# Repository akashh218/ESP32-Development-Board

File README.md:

# ESP32-WROOM Development Board

## Overview

This project is a custom ESP32-WROOM development board designed for embedded systems, IoT applications, robotics, and rapid prototyping. The board integrates essential support circuitry required for programming, debugging, power management, and peripheral interfacing, providing a reliable platform for ESP32-based development.

## Features

* ESP32-WROOM module
* USB Type-C interface for power and programming
* USB-to-UART converter for firmware upload and serial debugging
* 3.3V regulated power supply
* Reset and Boot buttons
* GPIO breakout headers
* I²C expansion support
* UART communication interface
* Motor driver connectivity
* Status and power indicator LEDs
* Compact and PCB-friendly design

## Hardware Specifications

| Parameter             | Value                                      |
| --------------------- | ------------------------------------------ |
| Microcontroller       | ESP32-WROOM                                |
| Operating Voltage     | 3.3V                                       |
| Input Power           | 5V USB Type-C                              |
| Wireless Connectivity | Wi-Fi 802.11 b/g/n, Bluetooth Classic, BLE |
| Programming Interface | USB-to-UART                                |
| GPIO Access           | Available through expansion headers        |

## Applications

* Home Automation
* IoT Devices
* Robotics
* Sensor Networks
* Industrial Monitoring
* Wireless Data Acquisition
* Smart Control Systems
* Embedded Learning and Prototyping

## PCB Design

The PCB was designed to provide:

* Stable power delivery
* Reliable ESP32 operation
* Easy firmware flashing
* Expansion for future peripherals
* Compact layout suitable for custom projects

## Repository Contents

* Schematics
* PCB Layout Files
* Gerber Files
* Bill of Materials (BOM)
* Assembly Documentation
* Hardware Images

## Getting Started

1. Connect the board using a USB Type-C cable.
2. Install ESP32 drivers if required.
3. Open Arduino IDE, PlatformIO, or ESP-IDF.
4. Select the appropriate ESP32 board configuration.
5. Upload your firmware.
6. Monitor serial output for debugging.

## Author

Designed and developed by Akash.

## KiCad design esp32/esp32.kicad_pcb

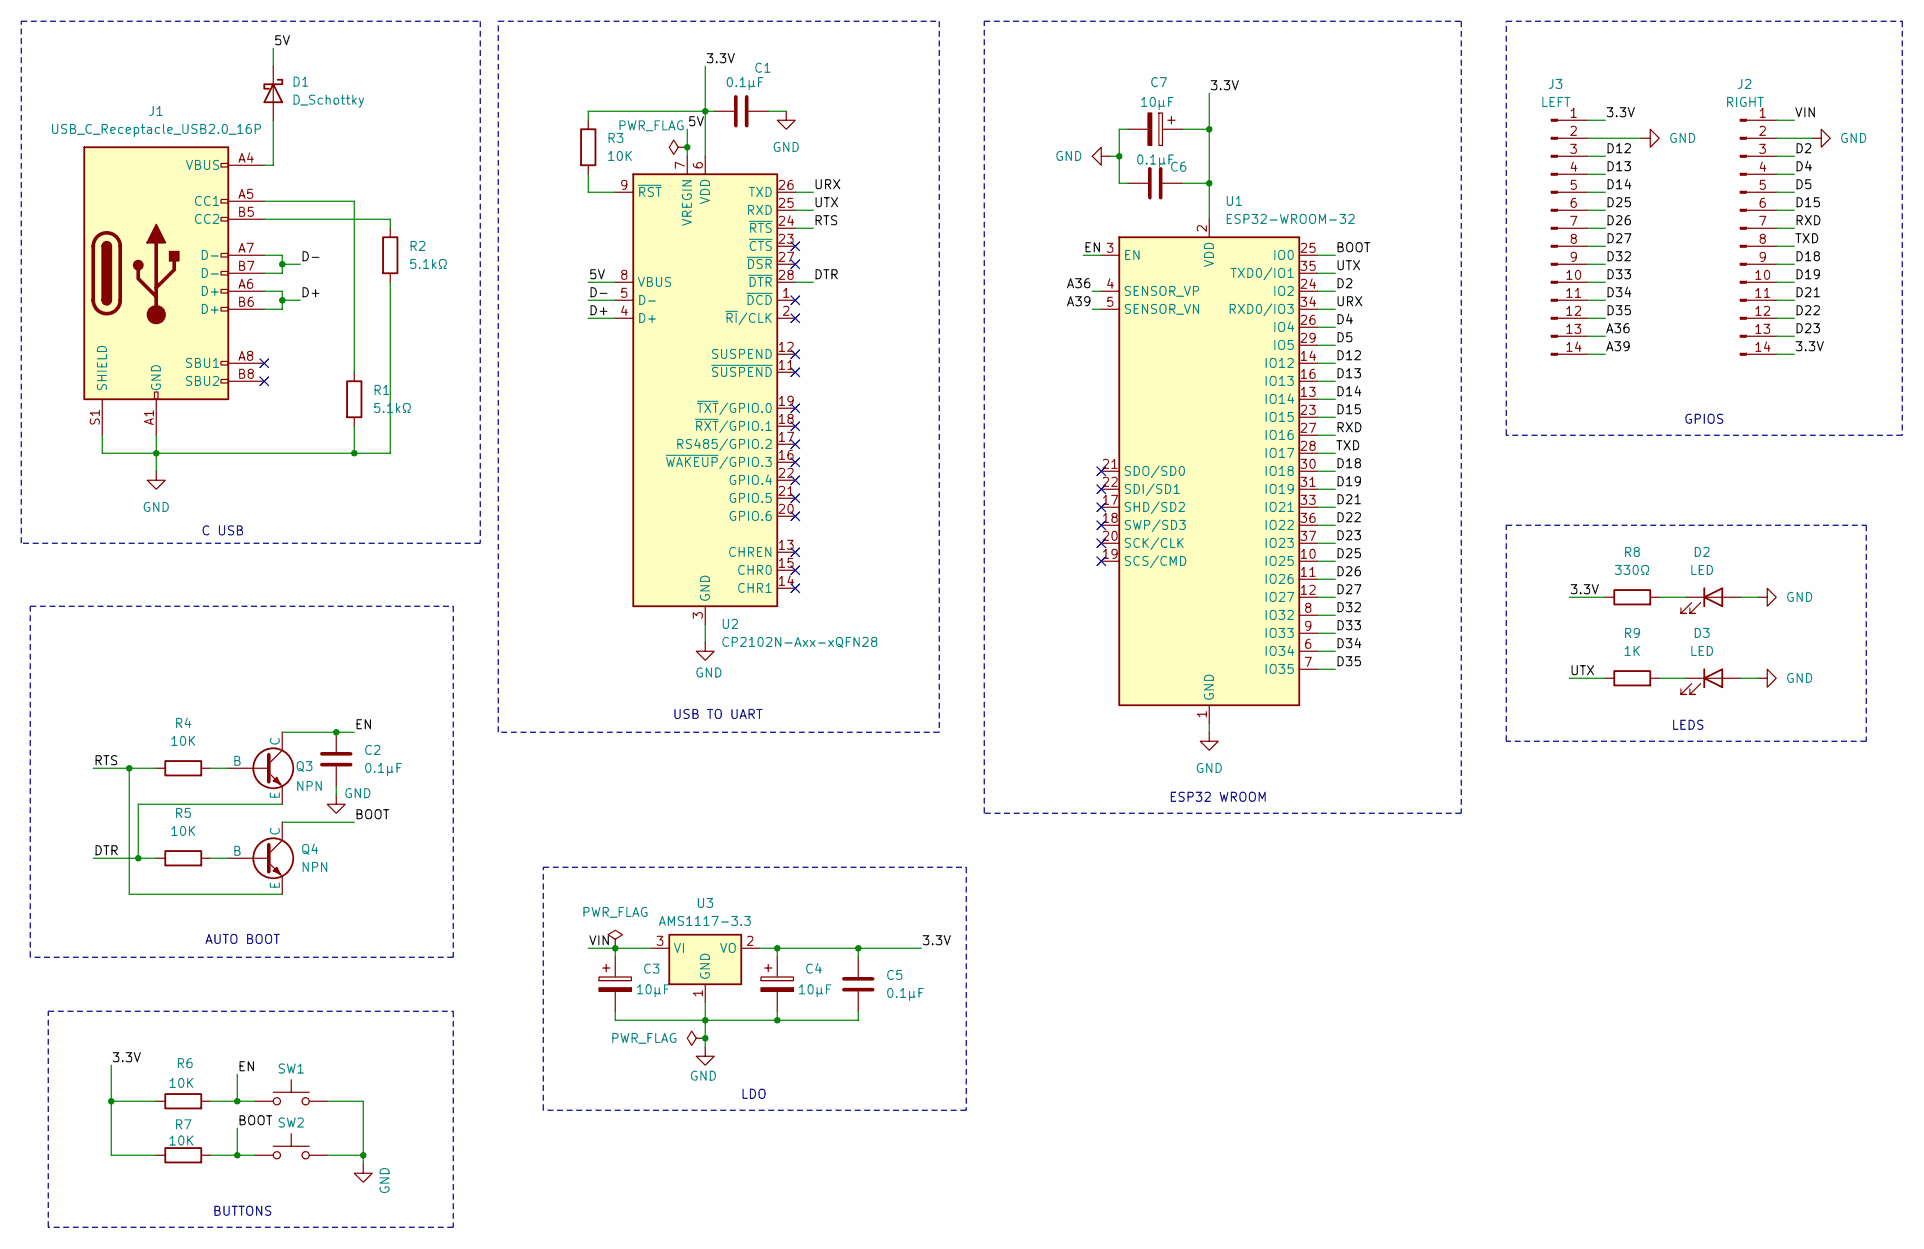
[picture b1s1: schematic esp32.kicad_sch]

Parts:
C1, C2, C5, C6: 0.1µF; C_0402_1005Metric
C3, C4, C7: 10µF; C_0805_2012Metric
D1: D_Schottky; D_SOD-123
D2, D3: LED; LED_0402_1005Metric
J1: USB_C_Receptacle_USB2.0_16P; USB_C_Receptacle_GCT_USB4085
J2: RIGHT; PinHeader_1x14_P2.54mm_Vertical
J3: LEFT; PinHeader_1x14_P2.54mm_Vertical
Q3, Q4: NPN; SOT-23
R1, R2: 5.1kΩ; R_0402_1005Metric
R3, R4, R5, R6, R7: 10K; R_0402_1005Metric
R8: 330Ω; R_0402_1005Metric
R9: 1K; R_0402_1005Metric
SW1, SW2: SW_Push; SW_Push_1P1T_NO_CK_KMR2
U1: ESP32-WROOM-32
U2: CP2102N-Axx-xQFN28; QFN-28-1EP_5x5mm_P0.5mm_EP3.35x3.35mm
U3: AMS1117-3.3; SOT-223-3_TabPin2

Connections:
/3.3V: C1.1, C4.1, C5.1, C6.2, C7.1, J2.14, J3.1, R3.1, R6.1, R7.1, R8.1, U1.2 (VDD), U2.6 (VDD), U3.2 (VO)
/5V: D1.1 (K), U2.7 (VREGIN), U2.8 (VBUS)
/A36: J3.13, U1.4 (SENSOR_VP)
/A39: J3.14, U1.5 (SENSOR_VN)
/BOOT: Q4.1 (C), R7.2, SW2.1, U1.25 (IO0); also elsewhere on the board
/D2: J2.3, U1.24 (IO2)
/D4: J2.4, U1.26 (IO4)
/D5: J2.5, U1.29 (IO5)
/D12: J3.3, U1.14 (IO12)
/D13: J3.4, U1.16 (IO13)
/D14: J3.5, U1.13 (IO14)
/D15: J2.6, U1.23 (IO15)
/D18: J2.9, U1.30 (IO18)
/D19: J2.10, U1.31 (IO19)
/D21: J2.11, U1.33 (IO21)
/D22: J2.12, U1.36 (IO22)
/D23: J2.13, U1.37 (IO23)
/D25: J3.6, U1.10 (IO25)
/D26: J3.7, U1.11 (IO26)
/D27: J3.8, U1.12 (IO27)
/D32: J3.9, U1.8 (IO32)
/D33: J3.10, U1.9 (IO33)
/D34: J3.11, U1.6 (IO34)
/D35: J3.12, U1.7 (IO35)
/D+: J1.A6 (D+), J1.B6 (D+), U2.4 (D+)
/D-: J1.A7 (D-), J1.B7 (D-), U2.5 (D-)
/DTR: Q3.3 (E), R5.1, U2.28 (~DTR)
/RTS: Q4.3 (E), R4.1, U2.24 (~RTS)
/RXD: J2.7, U1.27 (IO16)
/TXD: J2.8, U1.28 (IO17)
/URX: U1.34 (RXD0/IO3), U2.26 (TXD)
/UTX: R9.1, U1.35 (TXD0/IO1), U2.25 (RXD)
/VIN: C3.1, J2.1, U3.3 (VI)
unnamed: D1.2 (A), J1.A4 (VBUS), J1.A9 (VBUS), J1.B4 (VBUS), J1.B9 (VBUS)
unnamed: D2.1 (K), R8.2
unnamed: D3.1 (K), R9.2
unnamed: J1.A5 (CC1), R1.1
unnamed: J1.B5 (CC2), R2.1
unnamed: Q3.2 (B), R4.2
unnamed: Q4.2 (B), R5.2
unnamed: R3.2, U2.9 (~RST)

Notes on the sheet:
GPIOS
LEDS
AUTO BOOT
ESP32 WROOM
USB TO UART
C USB
BUTTONS
LDO

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
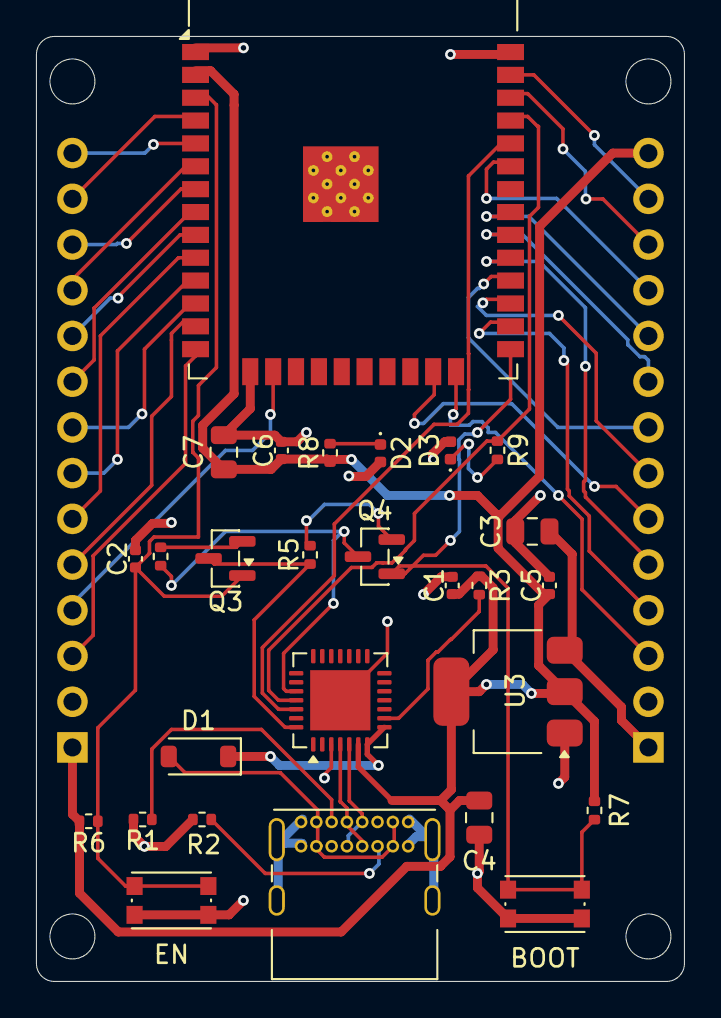
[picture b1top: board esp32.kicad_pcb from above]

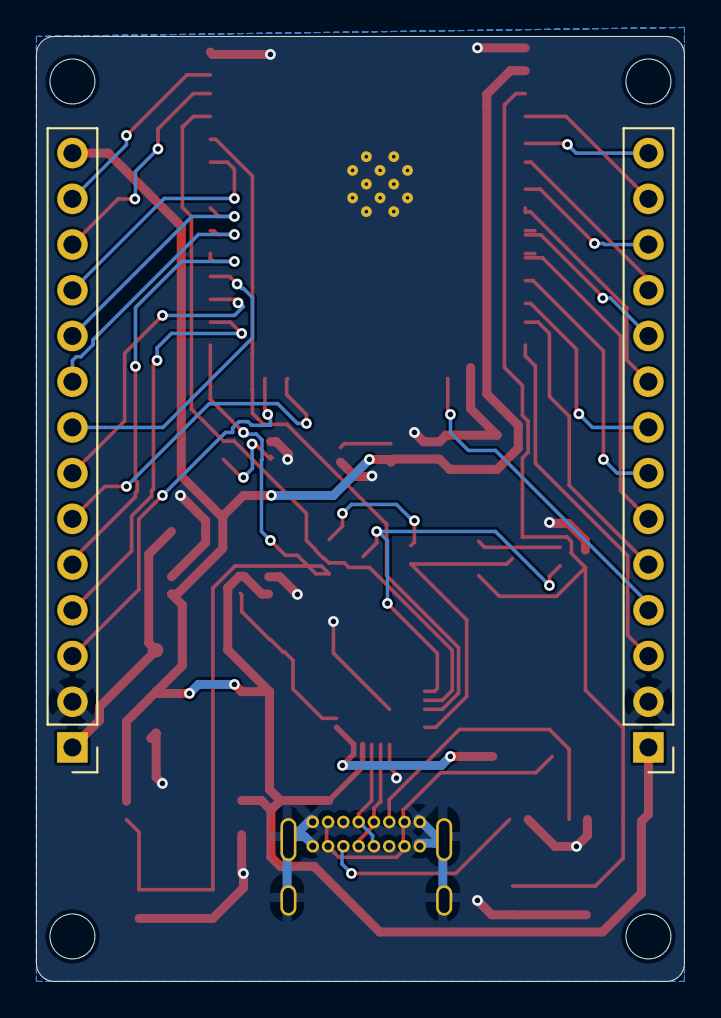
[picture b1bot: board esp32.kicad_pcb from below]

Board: 2 copper layers, 36.0 x 52.5 mm, 29 parts (2 on the bottom side), 43 nets.

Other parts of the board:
BOOT: SW_Push; SW_Push_1P1T_NO_CK_KMR2
EN: SW_Push; SW_Push_1P1T_NO_CK_KMR2

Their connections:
/BOOT: BOOT.1; also elsewhere on the board

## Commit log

2026-05-31 Revise README for ESP32-WROOM Development Board
    Updated README to reflect new project name and detailed features, specifications, and usage instructions for the ESP32-WROOM development board.
